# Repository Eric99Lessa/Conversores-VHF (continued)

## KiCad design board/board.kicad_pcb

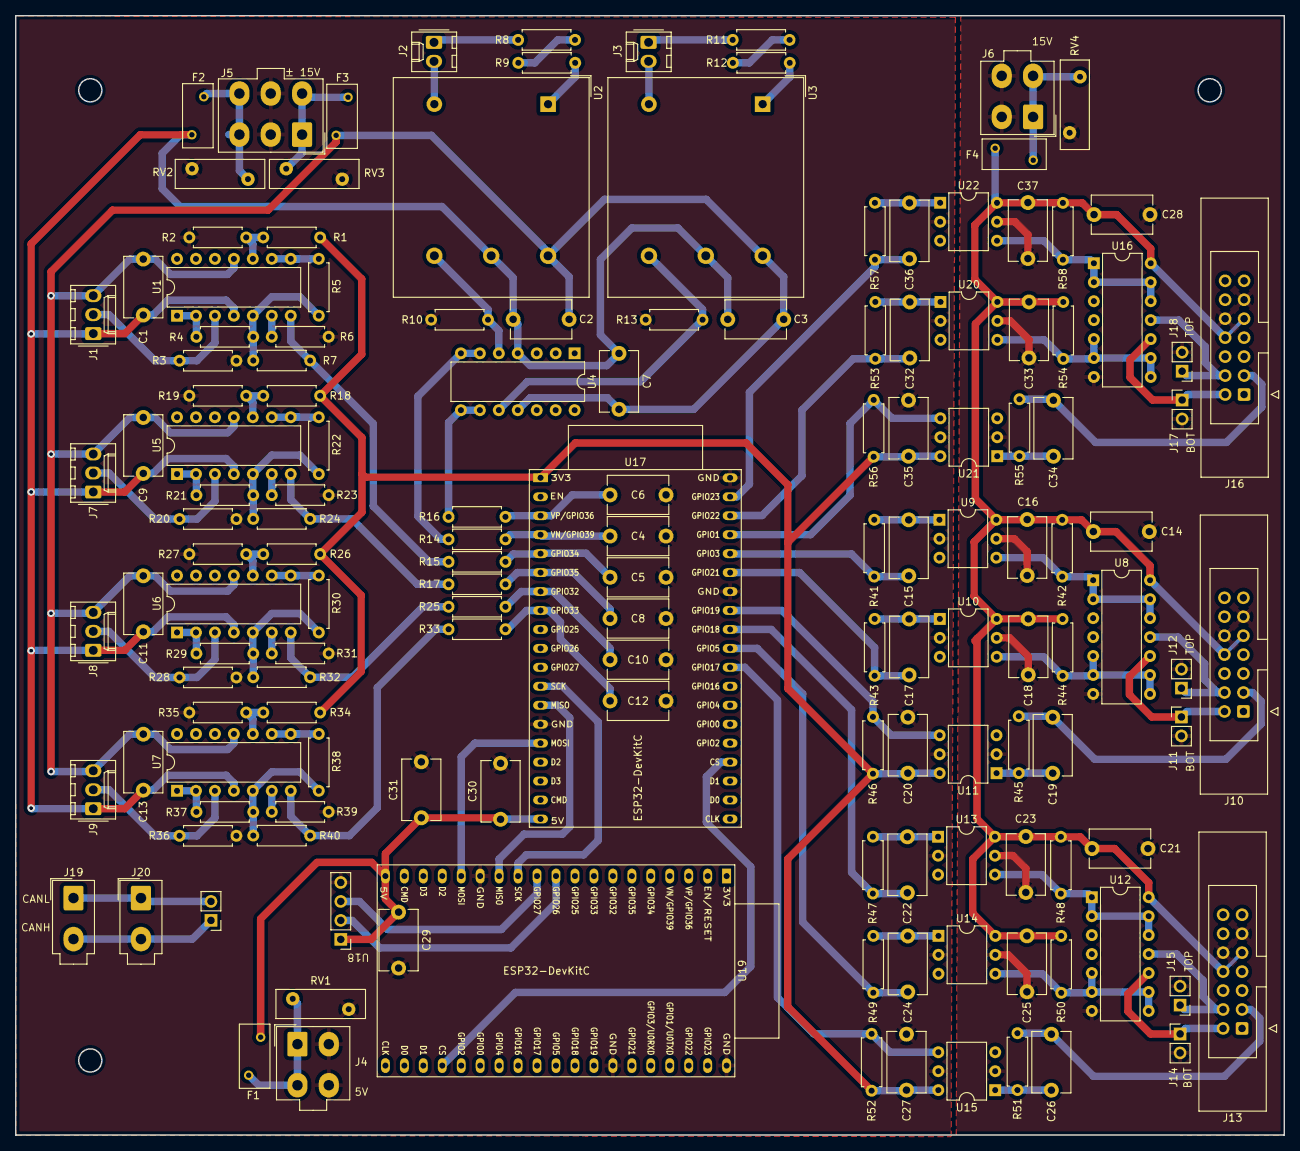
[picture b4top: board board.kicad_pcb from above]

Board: 2 copper layers, 170.0 x 150.0 mm, 145 parts (0 on the bottom side), 98 nets.

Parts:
C1, C2, C3, C7, C9, C11, C13, C14, C16, C18, C20, C21, C23, C25, C27, C28, C29, C30, C31, C33, C35, C37: 0,1u; C_Disc_D8.0mm_W5.0mm_P7.50mm
C4, C5, C6, C8, C10, C12: 330n; C_Disc_D8.0mm_W5.0mm_P7.50mm
C15, C17, C22, C24, C32, C36: C_pwm; C_Disc_D8.0mm_W5.0mm_P7.50mm
C19, C26, C34: C_err; C_Disc_D8.0mm_W5.0mm_P7.50mm
F1: 1A; Fuse_BelFuse_0ZRE0005FF_L8.3mm_W3.8mm
F2, F3: 0,4A; Fuse_BelFuse_0ZRE0005FF_L8.3mm_W3.8mm
F4: 3A; Fuse_BelFuse_0ZRE0005FF_L8.3mm_W3.8mm
J1, J7, J8, J9: Conn_01x03_Pin; Molex_KK-254_AE-6410-03A_1x03_P2.54mm_Vertical
J2, J3: Conn_01x02_Pin; Molex_KK-254_AE-6410-02A_1x02_P2.54mm_Vertical
J4, J6: Conn_02x02_ZigZag; Molex_Mini-Fit_Jr_5566-04A_2x02_P4.20mm_Vertical
J5: Conn_02x03_ZigZag; Molex_Mini-Fit_Jr_5566-06A_2x03_P4.20mm_Vertical
J10, J13, J16: Conn_02x07_Odd_Even; IDC-Header_2x07_P2.54mm_Latch_Vertical
J11, J12, J14, J15, J17, J18: Conn_01x02_Pin; PinHeader_1x02_P2.54mm_Vertical
J19, J20: Conn_01x02_Pin; Molex_Mini-Fit_Jr_5566-02A_2x01_P4.20mm_Vertical
R1, R2, R4, R5, R7, R18, R19, R21, R22, R24, R26, R27, R29, R30, R32, R34, R35, R37, R38, R40: 10k; R_Axial_DIN0207_L6.3mm_D2.5mm_P7.62mm_Horizontal
R3, R20, R28, R36: 47; R_Axial_DIN0207_L6.3mm_D2.5mm_P7.62mm_Horizontal
R6, R9, R11, R23, R31, R39: 3k3; R_Axial_DIN0207_L6.3mm_D2.5mm_P7.62mm_Horizontal
R8: 4k7; R_Axial_DIN0207_L6.3mm_D2.5mm_P7.62mm_Horizontal
R10, R13: 91; R_Axial_DIN0207_L6.3mm_D2.5mm_P7.62mm_Horizontal
R12: 2k7; R_Axial_DIN0207_L6.3mm_D2.5mm_P7.62mm_Horizontal
R14, R15, R16, R17, R25, R33: 1k; R_Axial_DIN0207_L6.3mm_D2.5mm_P7.62mm_Horizontal
R41, R43, R47, R49, R53, R57: 150; R_Axial_DIN0207_L6.3mm_D2.5mm_P7.62mm_Horizontal
R42, R44, R48, R50, R54, R58: 1k5; R_Axial_DIN0207_L6.3mm_D2.5mm_P7.62mm_Horizontal
R45, R51, R55: 1k2; R_Axial_DIN0207_L6.3mm_D2.5mm_P7.62mm_Horizontal
R46, R52, R56: 470; R_Axial_DIN0207_L6.3mm_D2.5mm_P7.62mm_Horizontal
RV1, RV2, RV3, RV4: Varistor; RV_Disc_D12mm_W3.9mm_P7.5mm
U1, U4, U5, U6, U7: LM324; DIP-14_W7.62mm
U2, U3: LV25-P; LEM_LV25-P
U8, U12, U16: HEF4093B; DIP-14_W7.62mm
U9, U10, U11, U13, U14, U15, U20, U21, U22: H11L1; DIP-6_W7.62mm
U17, U19: ESP32-DevKitC
U18: TJA1050

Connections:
+3.3V: C20.1, C27.1, C35.1, R1.1, R18.1, R26.1, R34.1, R46.1, R52.1, R56.1, U11.6, U15.6, U17.1 (3V3), U21.6
+5V: C29.1, C30.1, C31.1, F1.2, U17.19 (5V), U18.1 (VCC), U19.19 (5V)
+15V: C1.1, C2.1, C3.1, C7.1, C9.1, C11.1, C13.1, F2.2, J1.1, J7.1, J8.1, J9.1, U1.4 (V+), U2.5 (V+), U3.5 (V+), U4.4 (V+), U5.4 (V+), U6.4 (V+), U7.4 (V+)
-15V: C1.2, C2.2, C3.2, C7.2, C9.2, C11.2, C13.2, F3.2, J1.3, J7.3, J8.3, J9.3, U1.11 (V-), U2.6 (V-), U3.6 (V-), U4.11 (V-), U5.11 (V-), U6.11 (V-), U7.11 (V-)
/Adequação Sinais Corrente e Tensão/Filtro RC1/unfilt_signal: R14.1, U4.6 (-), U4.7
/Adequação Sinais Corrente e Tensão/Filtro RC2/unfilt_signal: R7.1, R15.1, U1.7
/Adequação Sinais Corrente e Tensão/Filtro RC3/unfilt_signal: R17.1, R24.1, U5.7
/Adequação Sinais Corrente e Tensão/Filtro RC4/unfilt_signal: R25.1, R32.1, U6.7
/Adequação Sinais Corrente e Tensão/Filtro RC5/unfilt_signal: R33.1, R40.1, U7.7
/Adequação Sinais Corrente e Tensão/Filtro RC/unfilt_signal: R16.1, U4.8, U4.9 (-)
/Adequação Sinais Corrente e Tensão/adequacao_sensor_tensao1/output_signal: R10.2, U2.4 (M), U4.5 (+)
/Adequação Sinais Corrente e Tensão/adequacao_sensor_tensao/output_signal: R13.2, U3.4 (M), U4.10 (+)
/I_read_L1: C5.1, R15.2, U17.5 (VDET_1/GPIO34/ADC1_CH6)
/I_read_L2: C8.1, R17.2, U17.6 (VDET_2/GPIO35/ADC1_CH7)
/I_read_L3: C10.1, R25.2, U17.7 (32K_XP/GPIO32/ADC1_CH4)
/I_read_out: C12.1, R33.2, U17.8 (32K_XN/GPIO33/ADC1_CH5)
/MicroControladores/CANH: J19.2, J20.2, U18.5 (CANH)
/MicroControladores/CANL: J19.1, J20.1, U18.6 (CANL)
/MicroControladores/CAN_RX: U18.3 (RX), U19.11 (ADC2_CH7/GPIO27)
/MicroControladores/CAN_TX: U18.2 (TX), U19.10 (DAC_2/ADC2_CH9/GPIO26)
/MicroControladores/CS: U17.23 (MTDO/GPIO15/ADC2_CH3), U19.23 (MTDO/GPIO15/ADC2_CH3)
/MicroControladores/MISO: U17.13 (MTDI/GPIO12/ADC2_CH5), U19.13 (MTDI/GPIO12/ADC2_CH5)
/MicroControladores/MOSI: U17.15 (MTCK/GPIO13/ADC2_CH4), U19.15 (MTCK/GPIO13/ADC2_CH4)
/MicroControladores/SCK: U17.12 (MTMS/GPIO14/ADC2_CH6), U19.12 (MTMS/GPIO14/ADC2_CH6)
/PWM - 15V Level Shifter/Conectores - PWM e erro1/Isolação de sinais - PWM6/out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: R44.2, U8.5, U8.6, U8.8, U8.9, U10.4
/PWM - 15V Level Shifter/Conectores - PWM e erro1/Isolação de sinais - PWM7/out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: R42.2, U8.1, U8.2, U8.12, U8.13, U9.4
/PWM - 15V Level Shifter/Conectores - PWM e erro1/PWM_BOT_driver: J10.2, J11.1, U8.10
/PWM - 15V Level Shifter/Conectores - PWM e erro1/PWM_TOP_driver: J10.4, J12.1, U8.11
/PWM - 15V Level Shifter/Conectores - PWM e erro1/erro_driver: C19.1, J10.3, R45.1
/PWM - 15V Level Shifter/Conectores - PWM e erro2/Isolação de sinais - PWM6/out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: R50.2, U12.5, U12.6, U12.8, U12.9, U14.4
/PWM - 15V Level Shifter/Conectores - PWM e erro2/Isolação de sinais - PWM7/out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: R48.2, U12.1, U12.2, U12.12, U12.13, U13.4
/PWM - 15V Level Shifter/Conectores - PWM e erro2/PWM_BOT_driver: J13.2, J14.1, U12.10
/PWM - 15V Level Shifter/Conectores - PWM e erro2/PWM_TOP_driver: J13.4, J15.1, U12.11
/PWM - 15V Level Shifter/Conectores - PWM e erro2/erro_driver: C26.1, J13.3, R51.1
/PWM - 15V Level Shifter/Conectores - PWM e erro/Isolação de sinais - PWM6/outp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: R54.2, U16.5, U16.6, U16.8, U16.9, U20.4
/PWM - 15V Level Shifter/Conectores - PWM e erro/Isolação de sinais - PWM7/outp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: R58.2, U16.1, U16.2, U16.12, U16.13, U22.4
/PWM - 15V Level Shifter/Conectores - PWM e erro/PWM_BOT_driver: J16.2, J17.1, U16.10
/PWM - 15V Level Shifter/Conectores - PWM e erro/PWM_TOP_driver: J16.4, J18.1, U16.11
/PWM - 15V Level Shifter/Conectores - PWM e erro/erro_driver: C34.1, J16.3, R55.1
/PWM_BOT_1: C32.1, R53.1, U17.36 (GPIO22)
/PWM_BOT_2: C17.1, R43.1, U17.33 (GPIO21)
/PWM_BOT_3: C24.1, R49.1, U17.29 (GPIO5)
/PWM_TOP_1: C36.1, R57.1, U17.37 (GPIO23)
/PWM_TOP_2: C15.1, R41.1, U17.34 (U0RXD/GPIO3)
/PWM_TOP_3: C22.1, R47.1, U17.30 (GPIO18)
/Power Connectors/5V_conn: F1.1, J4.1, J4.3, RV1.1
/Power Connectors/+15V_sym_conn: F2.1, J5.3, J5.6, RV2.1
/Power Connectors/-15V_sym_conn: F3.1, J5.1, J5.4, RV3.2
/Power Connectors/Vdrive_conn: F4.1, J6.1, J6.3, RV4.1
/V_read_in: C6.1, R16.2, U17.3 (SENSOR_VP/GPIO36/ADC1_CH0)
/V_read_out: C4.1, R14.2, U17.4 (SENSOR_VN/GPIO39/ADC1_CH3)
/err_1: R56.2, U17.35 (U0TXD/GPIO1), U21.4
/err_2: R46.2, U11.4, U17.31 (GPIO19)
/err_3: R52.2, U15.4, U17.28 (GPIO17)
GND: C4.2, C5.2, C6.2, C8.2, C10.2, C12.2, C20.2, C27.2, C29.2, C30.2, C31.2, C35.2, J4.2, J4.4, J5.2, J5.5, R2.2, R3.1, R6.2, R10.1, R13.1, R19.2, R20.1, R23.2, R27.2, R28.1, R31.2, R35.2, R36.1, R39.2, RV1.2, RV2.2, RV3.1, U9.2, U10.2, U11.5, U13.2, U14.2, U15.5, U17.14 (GND), U17.32 (GND), U17.38 (GND), U18.4 (GND), U19.14 (GND), U19.32 (GND), U19.38 (GND), U20.2, U21.5, U22.2
GND1: C14.2, C16.2, C18.2, C21.2, C23.2, C25.2, C28.2, C33.2, C37.2, J6.2, J6.4, J10.10, J10.11, J11.2, J12.2, J13.10, J13.11, J14.2, J15.2, J16.10, J16.11, J17.2, J18.2, RV4.2, U8.7 (GND), U9.5, U10.5, U11.2, U12.7 (GND), U13.5, U14.5, U15.2, U16.7 (GND), U20.5, U21.2, U22.5
unnamed: C15.2, R41.2, U9.1
unnamed: C17.2, R43.2, U10.1
unnamed: C19.2, R45.2, U11.1
unnamed: C22.2, R47.2, U13.1
unnamed: C24.2, R49.2, U14.1
unnamed: C26.2, R51.2, U15.1
unnamed: C32.2, R53.2, U20.1
unnamed: C34.2, R55.2, U21.1
unnamed: C36.2, R57.2, U22.1
unnamed: J1.2, R3.2, U1.3 (+)
unnamed: J2.1, R8.1
unnamed: J2.2, U2.3 (HV-)
unnamed: J3.1, R11.1
unnamed: J3.2, U3.3 (HV-)
unnamed: J7.2, R20.2, U5.3 (+)
unnamed: J8.2, R28.2, U6.3 (+)
unnamed: J9.2, R36.2, U7.3 (+)
unnamed: R8.2, R9.1
unnamed: R11.2, R12.1
unnamed: R4.2, U1.1, U1.2 (-)
unnamed: R4.1, R5.1, R7.2, U1.5 (+)
unnamed: R6.1, U1.6 (-)
unnamed: R1.2, R2.1, U1.10 (+)
unnamed: R5.2, U1.8, U1.9 (-)
unnamed: R9.2, U2.1 (HV+)
unnamed: R12.2, U3.1 (HV+)
unnamed: R21.2, U5.1, U5.2 (-)
unnamed: R21.1, R22.1, R24.2, U5.5 (+)
unnamed: R23.1, U5.6 (-)
unnamed: R18.2, R19.1, U5.10 (+)
unnamed: R22.2, U5.8, U5.9 (-)
unnamed: R29.2, U6.1, U6.2 (-)
unnamed: R29.1, R30.1, R32.2, U6.5 (+)
unnamed: R31.1, U6.6 (-)
unnamed: R26.2, R27.1, U6.10 (+)
unnamed: R30.2, U6.8, U6.9 (-)
unnamed: R37.2, U7.1, U7.2 (-)
unnamed: R37.1, R38.1, R40.2, U7.5 (+)
unnamed: R39.1, U7.6 (-)
unnamed: R34.2, R35.1, U7.10 (+)
unnamed: R38.2, U7.8, U7.9 (-)
Vdrive: C14.1, C16.1, C18.1, C21.1, C23.1, C25.1, C28.1, C33.1, C37.1, F4.2, J10.8, J10.9, J13.8, J13.9, J16.8, J16.9, R42.1, R44.1, R48.1, R50.1, R54.1, R58.1, U8.14 (VCC), U9.6, U10.6, U12.14 (VCC), U13.6, U14.6, U16.14 (VCC), U20.6, U22.6

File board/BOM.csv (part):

"Reference","Value","Datasheet","Footprint","Qty","DNP"
"C1","0,1u","~","Capacitor_THT:C_Disc_D8.0mm_W5.0mm_P7.50mm","1",""
"C2","0,1u","~","Capacitor_THT:C_Disc_D8.0mm_W5.0mm_P7.50mm","1",""
"C3","0,1u","~","Capacitor_THT:C_Disc_D8.0mm_W5.0mm_P7.50mm","1",""
"C4","330n","~","Capacitor_THT:C_Disc_D8.0mm_W5.0mm_P7.50mm","1",""
"C5","330n","~","Capacitor_THT:C_Disc_D8.0mm_W5.0mm_P7.50mm","1",""
"C6","330n","~","Capacitor_THT:C_Disc_D8.0mm_W5.0mm_P7.50mm","1",""
"C7","0,1u","~","Capacitor_THT:C_Disc_D8.0mm_W5.0mm_P7.50mm","1",""
"C8","330n","~","Capacitor_THT:C_Disc_D8.0mm_W5.0mm_P7.50mm","1",""
"C9","0,1u","~","Capacitor_THT:C_Disc_D8.0mm_W5.0mm_P7.50mm","1",""
"C10","330n","~","Capacitor_THT:C_Disc_D8.0mm_W5.0mm_P7.50mm","1",""
"C11","0,1u","~","Capacitor_THT:C_Disc_D8.0mm_W5.0mm_P7.50mm","1",""
"C12","330n","~","Capacitor_THT:C_Disc_D8.0mm_W5.0mm_P7.50mm","1",""
"C13","0,1u","~","Capacitor_THT:C_Disc_D8.0mm_W5.0mm_P7.50mm","1",""
"C14","0,1u","~","Capacitor_THT:C_Disc_D8.0mm_W5.0mm_P7.50mm","1",""
"C15","C_pwm","~","Capacitor_THT:C_Disc_D8.0mm_W5.0mm_P7.50mm","1",""
"C16","0,1u","~","Capacitor_THT:C_Disc_D8.0mm_W5.0mm_P7.50mm","1",""
"C17","C_pwm","~","Capacitor_THT:C_Disc_D8.0mm_W5.0mm_P7.50mm","1",""
"C18","0,1u","~","Capacitor_THT:C_Disc_D8.0mm_W5.0mm_P7.50mm","1",""
"C19","C_err","~","Capacitor_THT:C_Disc_D8.0mm_W5.0mm_P7.50mm","1",""
"C20","0,1u","~","Capacitor_THT:C_Disc_D8.0mm_W5.0mm_P7.50mm","1",""
"C21","0,1u","~","Capacitor_THT:C_Disc_D8.0mm_W5.0mm_P7.50mm","1",""
"C22","C_pwm","~","Capacitor_THT:C_Disc_D8.0mm_W5.0mm_P7.50mm","1",""
"C23","0,1u","~","Capacitor_THT:C_Disc_D8.0mm_W5.0mm_P7.50mm","1",""
"C24","C_pwm","~","Capacitor_THT:C_Disc_D8.0mm_W5.0mm_P7.50mm","1",""
"C25","0,1u","~","Capacitor_THT:C_Disc_D8.0mm_W5.0mm_P7.50mm","1",""
"C26","C_err","~","Capacitor_THT:C_Disc_D8.0mm_W5.0mm_P7.50mm","1",""
"C27","0,1u","~","Capacitor_THT:C_Disc_D8.0mm_W5.0mm_P7.50mm","1",""
"C28","0,1u","~","Capacitor_THT:C_Disc_D8.0mm_W5.0mm_P7.50mm","1",""
"C29","0,1u","~","Capacitor_THT:C_Disc_D8.0mm_W5.0mm_P7.50mm","1",""
"C30","0,1u","~","Capacitor_THT:C_Disc_D8.0mm_W5.0mm_P7.50mm","1",""
"C31","0,1u","~","Capacitor_THT:C_Disc_D8.0mm_W5.0mm_P7.50mm","1",""
"C32","C_pwm","~","Capacitor_THT:C_Disc_D8.0mm_W5.0mm_P7.50mm","1",""
"C33","0,1u","~","Capacitor_THT:C_Disc_D8.0mm_W5.0mm_P7.50mm","1",""
"C34","C_err","~","Capacitor_THT:C_Disc_D8.0mm_W5.0mm_P7.50mm","1",""
"C35","0,1u","~","Capacitor_THT:C_Disc_D8.0mm_W5.0mm_P7.50mm","1",""
"C36","C_pwm","~","Capacitor_THT:C_Disc_D8.0mm_W5.0mm_P7.50mm","1",""
"C37","0,1u","~","Capacitor_THT:C_Disc_D8.0mm_W5.0mm_P7.50mm","1",""
"F1","1A","~","Fuse:Fuse_BelFuse_0ZRE0005FF_L8.3mm_W3.8mm","1",""
"F2","0,4A","~","Fuse:Fuse_BelFuse_0ZRE0005FF_L8.3mm_W3.8mm","1",""
"F3","0,4A","~","Fuse:Fuse_BelFuse_0ZRE0005FF_L8.3mm_W3.8mm","1",""
"F4","3A","~","Fuse:Fuse_BelFuse_0ZRE0005FF_L8.3mm_W3.8mm","1",""
"J1","Conn_01x03_Pin","~","Connector_Molex:Molex_KK-254_AE-6410-03A_1x03_P2.54mm_Vertical","1",""
"J2","Conn_01x02_Pin","~","Connector_Molex:Molex_KK-254_AE-6410-02A_1x02_P2.54mm_Vertical","1",""
"J3","Conn_01x02_Pin","~","Connector_Molex:Molex_KK-254_AE-6410-02A_1x02_P2.54mm_Vertical","1",""
"J4","Conn_02x02_ZigZag","~","Modules:Molex_Mini-Fit_Jr_5566-04A_2x02_P4.20mm_Vertical","1",""
"J5","Conn_02x03_ZigZag","~","Modules:Molex_Mini-Fit_Jr_5566-06A_2x03_P4.20mm_Vertical","1",""
"J6","Conn_02x02_ZigZag","~","Modules:Molex_Mini-Fit_Jr_5566-04A_2x02_P4.20mm_Vertical","1",""
"J7","Conn_01x03_Pin","~","Connector_Molex:Molex_KK-254_AE-6410-03A_1x03_P2.54mm_Vertical","1",""
"J8","Conn_01x03_Pin","~","Connector_Molex:Molex_KK-254_AE-6410-03A_1x03_P2.54mm_Vertical","1",""
"J9","Conn_01x03_Pin","~","Connector_Molex:Molex_KK-254_AE-6410-03A_1x03_P2.54mm_Vertical","1",""
"J10","Conn_02x07_Odd_Even","~","Connector_IDC:IDC-Header_2x07_P2.54mm_Latch_Vertical","1",""
"J11","Conn_01x02_Pin","~","Connector_PinHeader_2.54mm:PinHeader_1x02_P2.54mm_Vertical","1",""
"J12","Conn_01x02_Pin","~","Connector_PinHeader_2.54mm:PinHeader_1x02_P2.54mm_Vertical","1",""
"J13","Conn_02x07_Odd_Even","~","Connector_IDC:IDC-Header_2x07_P2.54mm_Latch_Vertical","1",""
"J14","Conn_01x02_Pin","~","Connector_PinHeader_2.54mm:PinHeader_1x02_P2.54mm_Vertical","1",""
"J15","Conn_01x02_Pin","~","Connector_PinHeader_2.54mm:PinHeader_1x02_P2.54mm_Vertical","1",""
"J16","Conn_02x07_Odd_Even","~","Connector_IDC:IDC-Header_2x07_P2.54mm_Latch_Vertical","1",""
"J17","Conn_01x02_Pin","~","Connector_PinHeader_2.54mm:PinHeader_1x02_P2.54mm_Vertical","1",""
"J18","Conn_01x02_Pin","~","Connector_PinHeader_2.54mm:PinHeader_1x02_P2.54mm_Vertical","1",""
"J19","Conn_01x02_Pin","~","Modules:Molex_Mini-Fit_Jr_5566-02A_2x01_P4.20mm_Vertical","1",""
"J20","Conn_01x02_Pin","~","Modules:Molex_Mini-Fit_Jr_5566-02A_2x01_P4.20mm_Vertical","1",""
"R1","10k","~","Resistor_THT:R_Axial_DIN0207_L6.3mm_D2.5mm_P7.62mm_Horizontal","1",""
"R2","10k","~","Resistor_THT:R_Axial_DIN0207_L6.3mm_D2.5mm_P7.62mm_Horizontal","1",""
"R3","47","~","Resistor_THT:R_Axial_DIN0207_L6.3mm_D2.5mm_P7.62mm_Horizontal","1",""
"R4","10k","~","Resistor_THT:R_Axial_DIN0207_L6.3mm_D2.5mm_P7.62mm_Horizontal","1",""
"R5","10k","~","Resistor_THT:R_Axial_DIN0207_L6.3mm_D2.5mm_P7.62mm_Horizontal","1",""
"R6","3k3","~","Resistor_THT:R_Axial_DIN0207_L6.3mm_D2.5mm_P7.62mm_Horizontal","1",""
"R7","10k","~","Resistor_THT:R_Axial_DIN0207_L6.3mm_D2.5mm_P7.62mm_Horizontal","1",""
"R8","4k7","~","Resistor_THT:R_Axial_DIN0207_L6.3mm_D2.5mm_P7.62mm_Horizontal","1",""
"R9","3k3","~","Resistor_THT:R_Axial_DIN0207_L6.3mm_D2.5mm_P7.62mm_Horizontal","1",""
"R10","91","~","Resistor_THT:R_Axial_DIN0207_L6.3mm_D2.5mm_P7.62mm_Horizontal","1",""
"R11","3k3","~","Resistor_THT:R_Axial_DIN0207_L6.3mm_D2.5mm_P7.62mm_Horizontal","1",""
"R12","2k7","~","Resistor_THT:R_Axial_DIN0207_L6.3mm_D2.5mm_P7.62mm_Horizontal","1",""
"R13","91","~","Resistor_THT:R_Axial_DIN0207_L6.3mm_D2.5mm_P7.62mm_Horizontal","1",""
"R14","1k","~","Resistor_THT:R_Axial_DIN0207_L6.3mm_D2.5mm_P7.62mm_Horizontal","1",""
"R15","1k","~","Resistor_THT:R_Axial_DIN0207_L6.3mm_D2.5mm_P7.62mm_Horizontal","1",""
"R16","1k","~","Resistor_THT:R_Axial_DIN0207_L6.3mm_D2.5mm_P7.62mm_Horizontal","1",""
"R17","1k","~","Resistor_THT:R_Axial_DIN0207_L6.3mm_D2.5mm_P7.62mm_Horizontal","1",""
"R18","10k","~","Resistor_THT:R_Axial_DIN0207_L6.3mm_D2.5mm_P7.62mm_Horizontal","1",""
"R19","10k","~","Resistor_THT:R_Axial_DIN0207_L6.3mm_D2.5mm_P7.62mm_Horizontal","1",""
"R20","47","~","Resistor_THT:R_Axial_DIN0207_L6.3mm_D2.5mm_P7.62mm_Horizontal","1",""
"R21","10k","~","Resistor_THT:R_Axial_DIN0207_L6.3mm_D2.5mm_P7.62mm_Horizontal","1",""
"R22","10k","~","Resistor_THT:R_Axial_DIN0207_L6.3mm_D2.5mm_P7.62mm_Horizontal","1",""
"R23","3k3","~","Resistor_THT:R_Axial_DIN0207_L6.3mm_D2.5mm_P7.62mm_Horizontal","1",""
"R24","10k","~","Resistor_THT:R_Axial_DIN0207_L6.3mm_D2.5mm_P7.62mm_Horizontal","1",""
"R25","1k","~","Resistor_THT:R_Axial_DIN0207_L6.3mm_D2.5mm_P7.62mm_Horizontal","1",""
"R26","10k","~","Resistor_THT:R_Axial_DIN0207_L6.3mm_D2.5mm_P7.62mm_Horizontal","1",""
"R27","10k","~","Resistor_THT:R_Axial_DIN0207_L6.3mm_D2.5mm_P7.62mm_Horizontal","1",""
"R28","47","~","Resistor_THT:R_Axial_DIN0207_L6.3mm_D2.5mm_P7.62mm_Horizontal","1",""
"R29","10k","~","Resistor_THT:R_Axial_DIN0207_L6.3mm_D2.5mm_P7.62mm_Horizontal","1",""
"R30","10k","~","Resistor_THT:R_Axial_DIN0207_L6.3mm_D2.5mm_P7.62mm_Horizontal","1",""
"R31","3k3","~","Resistor_THT:R_Axial_DIN0207_L6.3mm_D2.5mm_P7.62mm_Horizontal","1",""
"R32","10k","~","Resistor_THT:R_Axial_DIN0207_L6.3mm_D2.5mm_P7.62mm_Horizontal","1",""
"R33","1k","~","Resistor_THT:R_Axial_DIN0207_L6.3mm_D2.5mm_P7.62mm_Horizontal","1",""
"R34","10k","~","Resistor_THT:R_Axial_DIN0207_L6.3mm_D2.5mm_P7.62mm_Horizontal","1",""
"R35","10k","~","Resistor_THT:R_Axial_DIN0207_L6.3mm_D2.5mm_P7.62mm_Horizontal","1",""
"R36","47","~","Resistor_THT:R_Axial_DIN0207_L6.3mm_D2.5mm_P7.62mm_Horizontal","1",""
"R37","10k","~","Resistor_THT:R_Axial_DIN0207_L6.3mm_D2.5mm_P7.62mm_Horizontal","1",""
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
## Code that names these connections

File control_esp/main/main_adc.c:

#include <string.h>
#include "freertos/FreeRTOS.h"
#include "freertos/task.h"
#include "driver/adc.h"
#include "esp_log.h"

static const char *TAG_ADC = "ADC";

#define ADC_SAMPLES_PER_CH 2
#define ADC_WIDTH_CFG ADC_WIDTH_BIT_12
#define ADC_ATTEN_CFG ADC_ATTEN_DB_11

typedef enum
{
    ADC_SIG_V_IN = 0,
    ADC_SIG_V_OUT,
    ADC_SIG_IL1,
    ADC_SIG_IL2,
    ADC_SIG_IL3,
    ADC_SIG_IL_OUT,
    ADC_SIG_COUNT
} adc_signal_t;

static const char *s_adc_sig_name[ADC_SIG_COUNT] = {
    "V_in", "V_out", "IL1", "IL2", "IL3", "IL_out"};

static const adc1_channel_t s_adc1_sig_channel[ADC_SIG_COUNT] = {
    [ADC_SIG_V_IN] = ADC1_CHANNEL_0,   // GPIO36
    [ADC_SIG_V_OUT] = ADC1_CHANNEL_3,  // GPIO39
    [ADC_SIG_IL1] = ADC1_CHANNEL_6,    // GPIO34
    [ADC_SIG_IL2] = ADC1_CHANNEL_7,    // GPIO35
    [ADC_SIG_IL3] = ADC1_CHANNEL_4,    // GPIO32
    [ADC_SIG_IL_OUT] = ADC1_CHANNEL_5, // GPIO33
};

static void adc1_init_legacy(void)
{
    adc1_config_width(ADC_WIDTH_CFG);
    for (int i = 0; i < ADC_SIG_COUNT; i++)
    {
        adc1_config_channel_atten(s_adc1_sig_channel[i], ADC_ATTEN_CFG);
    }
    ESP_LOGI(TAG_ADC, "ADC1 configured (legacy). TickHz=%d", configTICK_RATE_HZ);
}

static inline int adc1_read_avg(adc1_channel_t ch, int samples)
{
    uint32_t sum = 0;
    for (int i = 0; i < samples; i++)
    {
        sum += adc1_get_raw(ch);
    }
    return (int)(sum / samples);
}

static void adc_task(void *arg)
{
    (void)arg;
    adc1_init_legacy();

    while (1)
    {
        int v[ADC_SIG_COUNT];
        for (int i = 0; i < ADC_SIG_COUNT; i++)
        {
            v[i] = adc1_read_avg(s_adc1_sig_channel[i], ADC_SAMPLES_PER_CH);
        }

        ESP_LOGI(TAG_ADC,
                 "%s=%d %s=%d %s=%d %s=%d %s=%d %s=%d",
                 s_adc_sig_name[ADC_SIG_V_IN], v[ADC_SIG_V_IN],
                 s_adc_sig_name[ADC_SIG_V_OUT], v[ADC_SIG_V_OUT],
                 s_adc_sig_name[ADC_SIG_IL1], v[ADC_SIG_IL1],
                 s_adc_sig_name[ADC_SIG_IL2], v[ADC_SIG_IL2],
                 s_adc_sig_name[ADC_SIG_IL3], v[ADC_SIG_IL3],
                 s_adc_sig_name[ADC_SIG_IL_OUT], v[ADC_SIG_IL_OUT]);

        vTaskDelay(pdMS_TO_TICKS(100));
    }
}

void app_main(void)
{
    xTaskCreate(adc_task, "adc", 4096, NULL, 5, NULL);
}

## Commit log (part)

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2025-09-12 Initial commit: add KiCad project
2025-09-16 Schematic changes: correct micro board and subsystems
2025-09-17 Schematic changes: Complete PWM voltage level shifter
2025-09-18 Schematic changes: Fix optocoupler output, fix resistor values
2025-09-27 Schematic changes and board creation
2025-10-01 Finalização da placa, trilhas, planos de terra e footprint TJA1050
2025-10-08 Criação da placa de alimentação
2025-10-10 Reorganização de pastas, udate da placa de alimentação
2025-10-14 Adição de circuitos opcionais para PWM
2025-10-30 Modificações nas duas placas, adição de furos para montagem, melhora na posição dos micros e conectores para comunicação SPI
2025-11-06 Criação de novas pastas com código em C e Matlab
2026-01-12 Criação dos arquivos em C para o firmware dos dois micros e script em python para salvar aquisição dos dados e envio de comandos
2026-01-29 Mudanças no firmware e calibração da tensão de entrada e saída
2026-05-16 Plataforma Semikron no Simulink, simulações de controle IDAPBC, Cascata e Krasovskii
